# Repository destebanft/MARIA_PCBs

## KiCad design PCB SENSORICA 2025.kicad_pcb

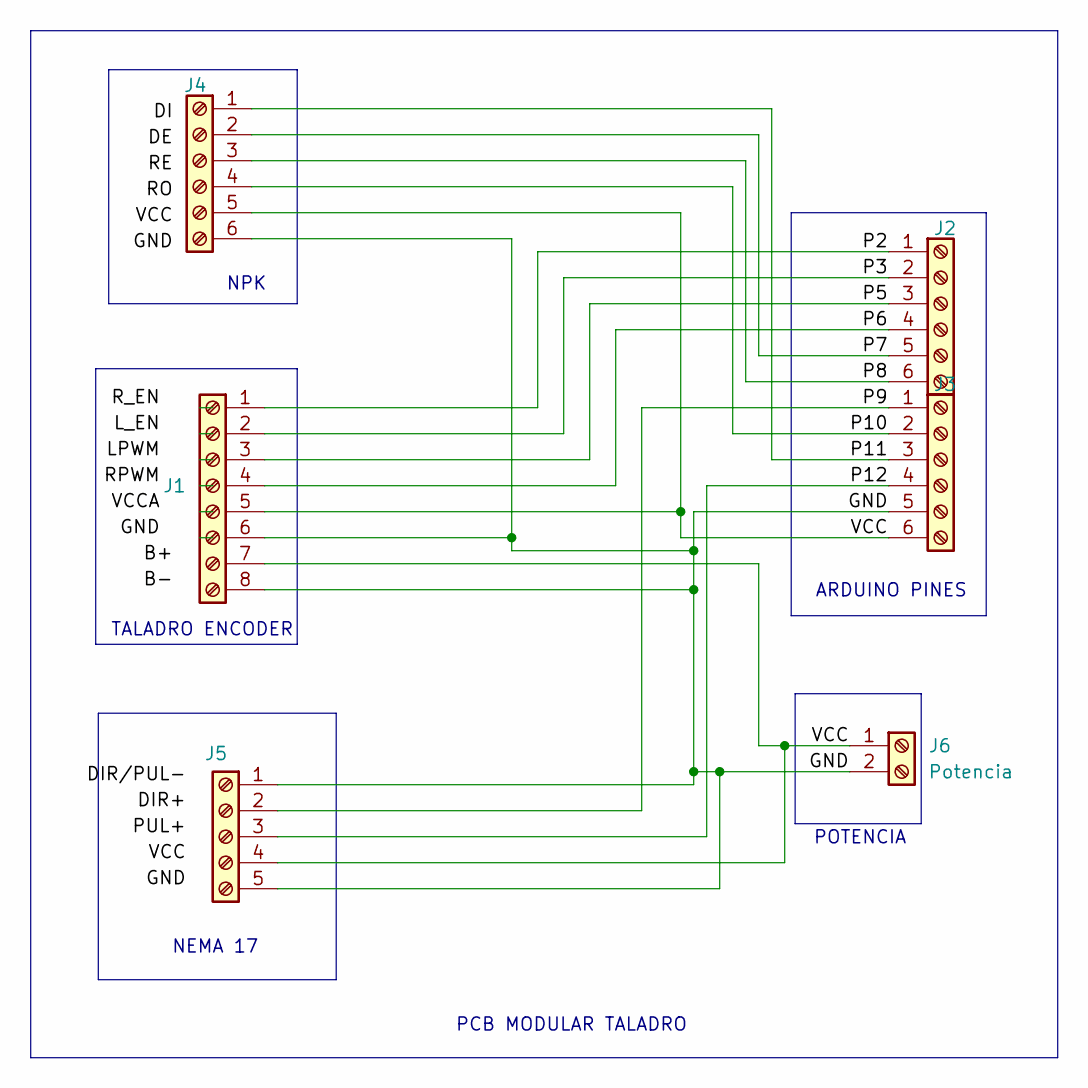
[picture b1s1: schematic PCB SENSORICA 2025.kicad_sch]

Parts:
J1: Taladro Encoder; TerminalBlock_bornier-8_P5.08mm
J2: Arduino_2; TerminalBlock_bornier-6_P5.08mm
J3: Arduino_1; TerminalBlock_bornier-6_P5.08mm
J4: NPK; TerminalBlock_bornier-6_P5.08mm
J5: Nema 17; TerminalBlock_bornier-5_P5.08mm
J6: Potencia; TerminalBlock_bornier-2_P5.08mm

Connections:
/GND: J1.6, J1.8, J3.5, J4.6, J5.1, J5.5, J6.2
/P2: J1.1, J2.1
/P3: J1.2, J2.2
/P5: J1.3, J2.3
/P6: J1.4, J2.4
/P7: J2.5, J4.2
/P8: J2.6, J4.3
/P9: J3.1, J5.2
/P10: J3.2, J4.4
/P11: J3.3, J4.1
/P12: J3.4, J5.3
/VCC: J1.5, J1.7, J3.6, J4.5, J5.4, J6.1

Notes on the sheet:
POTENCIA
NPK
PCB MODULAR TALADRO
TALADRO ENCODER
NEMA 17
ARDUINO PINES

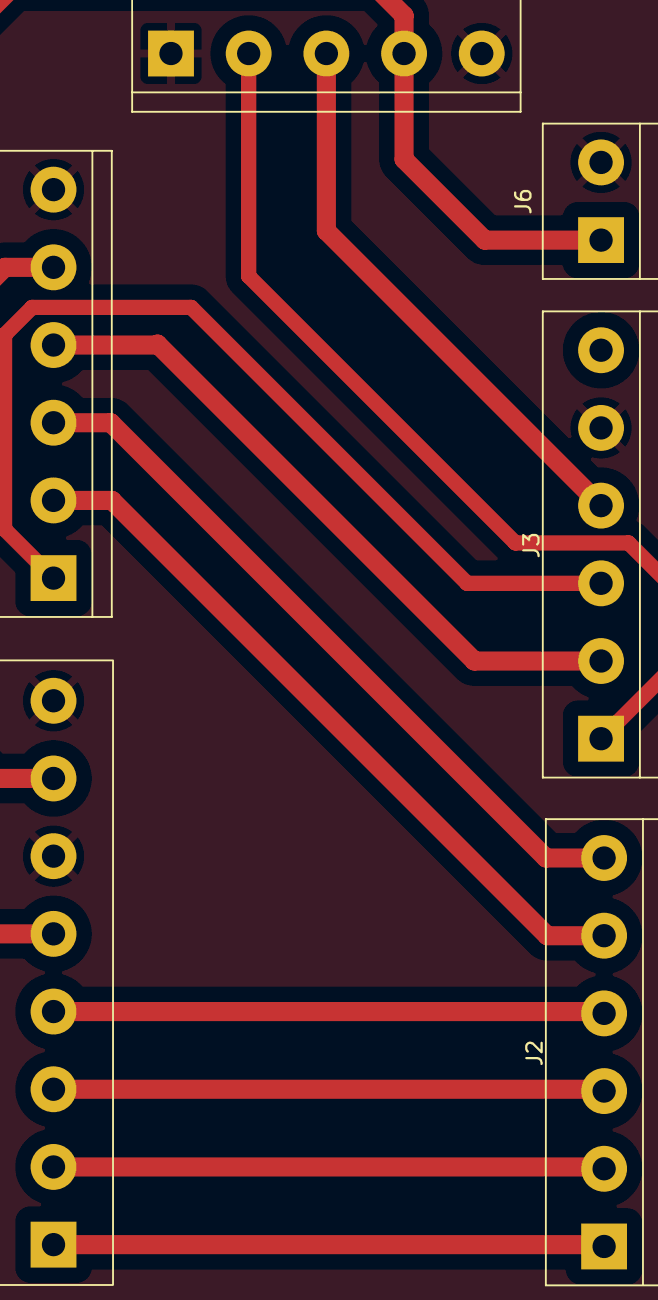
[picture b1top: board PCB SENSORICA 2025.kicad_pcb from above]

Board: 2 copper layers, 6 parts (0 on the bottom side), 12 nets.

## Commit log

2025-04-27 Upñoad files
2025-04-28 Generación de los archivos .drl
